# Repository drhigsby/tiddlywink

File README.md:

# tiddlywink

An angled, unibody QAZ-like 40% keyboard with 38 keys and two optional rotary encoder positions.

## Hardware

| Component | Qty | Notes |
|---|---|---|
| MX Switches | 38 | 5-pin highly recommended |
| Diodes | 38 | SOD-123 |
| Pro Micro or equivalent | 1 | ATmega32U4, USB-C recommended |
| Low Profile Binding Barrels | 5 | https://www.mcmaster.com/93121A330/ |
| RGB LEDs | 10 | Optional — WS2812B-B |
| Rotary Encoder | 1 | Optional — Alps EC11, two positions available |
| Reset Button | 1 | Optional — SMD SW_SPST_SKQG https://www.amazon.com/gp/product/B07JM32QQW/ |

## Firmware

This keyboard runs [VIAL](https://get.vial.today) firmware for live keymap editing.

Firmware source files are in the `firmware/` folder and are also submitted to [vial-qmk](https://github.com/vial-kb/vial-qmk).

To compile:
\`\`\`bash
qmk compile -kb drhigsby/tiddlywink -km vial -c
\`\`\`

## Repository Structure

\`\`\`
tiddlywink/
├── firmware/       # QMK/VIAL firmware source files
├── hardware/       # KiCad schematic and PCB files
├── gerbers/        # Gerber files for PCB fabrication
│   ├── angled/     # Original angled variant
│   └── square/     # Square variant
└── case/           # Case DXF files
\`\`\`

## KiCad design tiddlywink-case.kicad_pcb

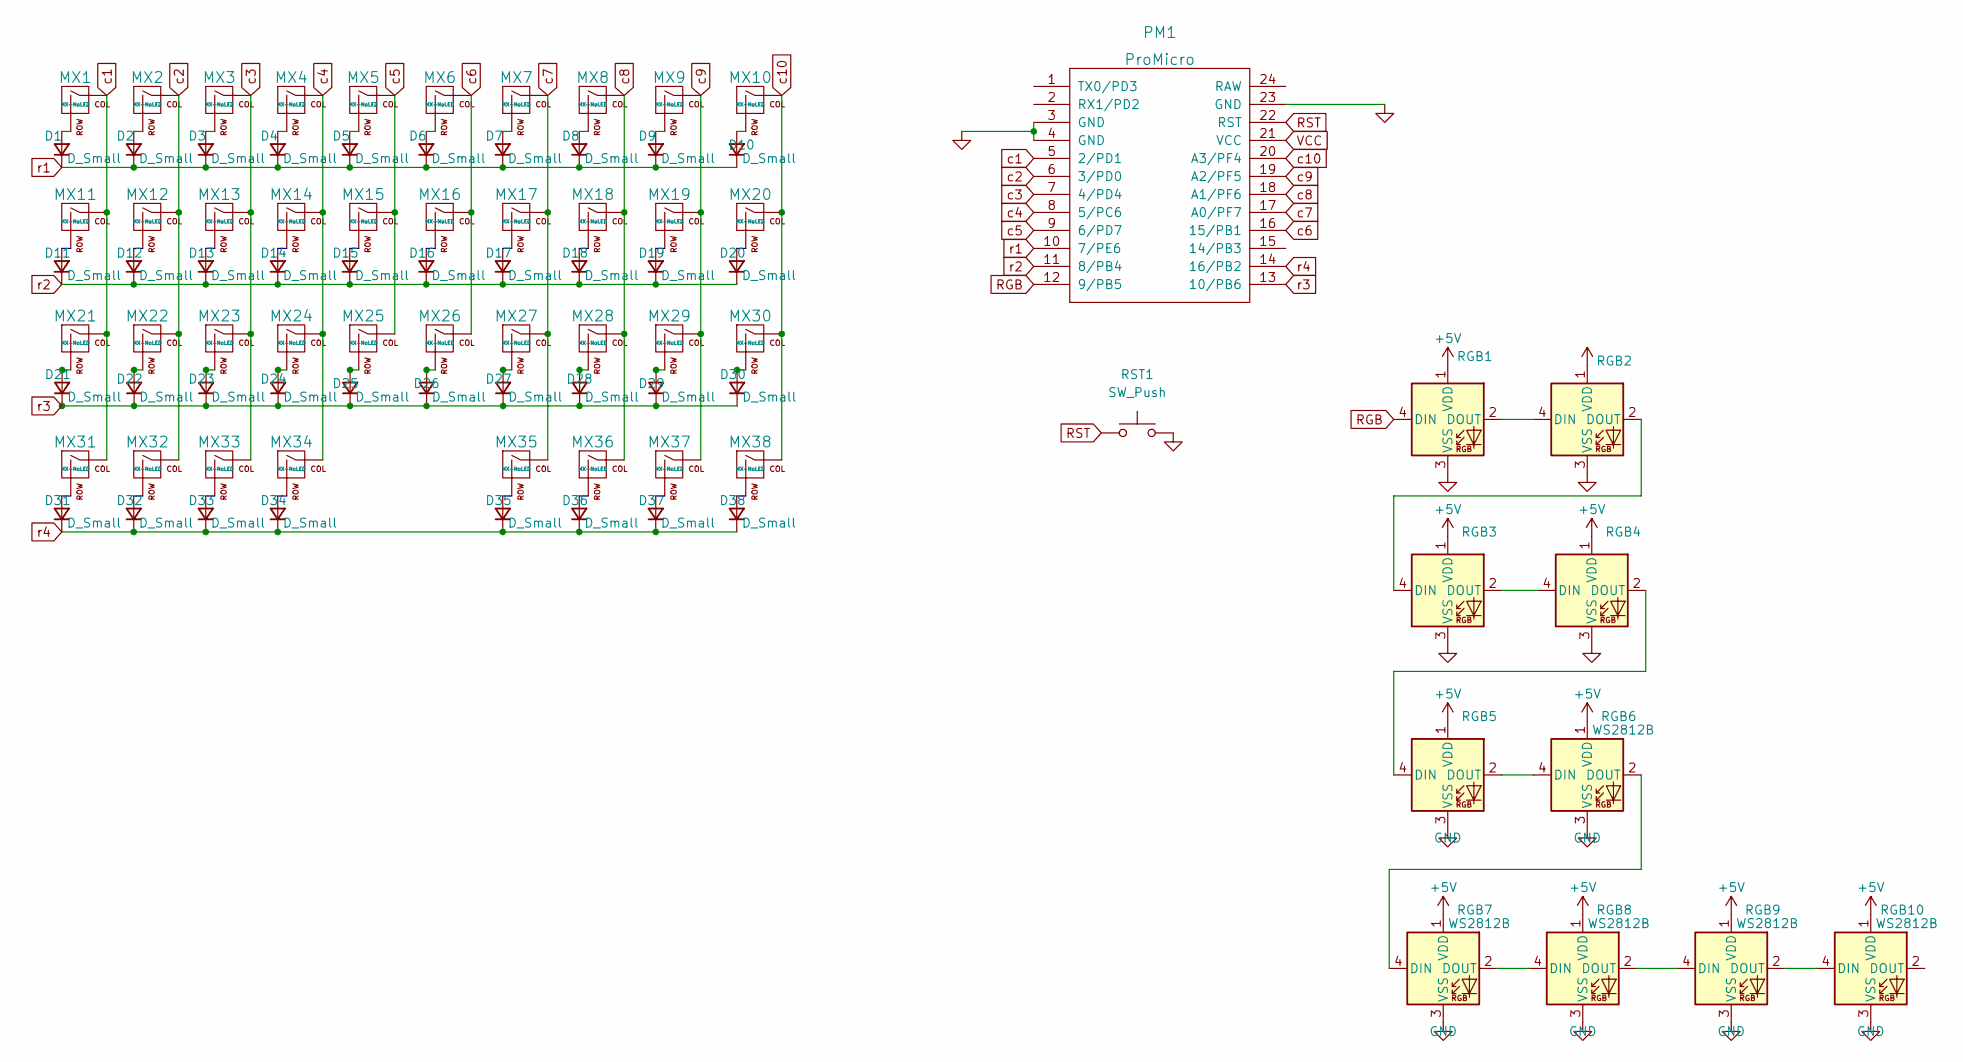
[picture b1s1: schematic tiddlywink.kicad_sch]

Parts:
D1, D2, D3, D4, D5, D6, D7, D8, D9, D10, D11, D12, D13, D14, D15, D16, D17, D18, D19, D20, D21, D22, D23, D24, D25, D26, D27, D28, D29, D30, D31, D32, D33, D34, D35, D36, D37, D38: D_Small; D_SOD123_via
MX1, MX2, MX3, MX4, MX5, MX6, MX7, MX8, MX9, MX12, MX13, MX14, MX15, MX16, MX17, MX18, MX19, MX20, MX22, MX23, MX24, MX25, MX26, MX27, MX28, MX29, MX32, MX33, MX36, MX37: MX-NoLED; MXOnly-1U-NoLED
MX10, MX11, MX31, MX38: MX-NoLED; MXOnly-1.25U-NoLED
MX21, MX34, MX35: MX-NoLED; MXOnly-1.75U-NoLED
MX30: MX-NoLED; MXOnly-1.5U-NoLED
PM1: ProMicro; ArduinoProMicro
RGB1, RGB2, RGB3, RGB4, RGB5: (no value)
RGB6, RGB7, RGB8, RGB9, RGB10: WS2812B; LED_WS2812B_PLCC4_5.0x5.0mm_P3.2mm
RST1: SW_Push; SW_SPST_TL3342

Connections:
unnamed: D1.2 (A), MX1.2 (ROW)
unnamed: D2.2 (A), MX2.2 (ROW)
unnamed: D3.2 (A), MX3.2 (ROW)
unnamed: D4.2 (A), MX4.2 (ROW)
unnamed: D5.2 (A), MX5.2 (ROW)
unnamed: D6.2 (A), MX6.2 (ROW)
unnamed: D7.2 (A), MX7.2 (ROW)
unnamed: D8.2 (A), MX8.2 (ROW)
unnamed: D9.2 (A), MX9.2 (ROW)
unnamed: D10.2 (A), MX10.2 (ROW)
unnamed: D11.2 (A), MX11.2 (ROW)
unnamed: D12.2 (A), MX12.2 (ROW)
unnamed: D13.2 (A), MX13.2 (ROW)
unnamed: D14.2 (A), MX14.2 (ROW)
unnamed: D15.2 (A), MX15.2 (ROW)
unnamed: D16.2 (A), MX16.2 (ROW)
unnamed: D17.2 (A), MX17.2 (ROW)
unnamed: D18.2 (A), MX18.2 (ROW)
unnamed: D19.2 (A), MX19.2 (ROW)
unnamed: D20.2 (A), MX20.2 (ROW)
unnamed: D21.2 (A), MX21.2 (ROW)
unnamed: D22.2 (A), MX22.2 (ROW)
unnamed: D23.2 (A), MX23.2 (ROW)
unnamed: D24.2 (A), MX24.2 (ROW)
unnamed: D25.2 (A), MX25.2 (ROW)
unnamed: D26.2 (A), MX26.2 (ROW)
unnamed: D27.2 (A), MX27.2 (ROW)
unnamed: D28.2 (A), MX28.2 (ROW)
unnamed: D29.2 (A), MX29.2 (ROW)
unnamed: D30.2 (A), MX30.2 (ROW)
unnamed: D31.2 (A), MX31.2 (ROW)
unnamed: D32.2 (A), MX32.2 (ROW)
unnamed: D33.2 (A), MX33.2 (ROW)
unnamed: D34.2 (A), MX34.2 (ROW)
unnamed: D35.2 (A), MX35.2 (ROW)
unnamed: D36.2 (A), MX36.2 (ROW)
unnamed: D37.2 (A), MX37.2 (ROW)
unnamed: D38.2 (A), MX38.2 (ROW)
unnamed: RGB1.2 (DOUT), RGB2.4 (DIN)
unnamed: RGB2.2 (DOUT), RGB3.4 (DIN)
unnamed: RGB3.2 (DOUT), RGB4.4 (DIN)
unnamed: RGB4.2 (DOUT), RGB5.4 (DIN)
unnamed: RGB5.2 (DOUT), RGB6.4 (DIN)
unnamed: RGB6.2 (DOUT), RGB7.4 (DIN)
unnamed: RGB8.2 (DOUT), RGB9.4 (DIN)
unnamed: RGB7.2 (DOUT), RGB8.4 (DIN)
unnamed: RGB9.2 (DOUT), RGB10.4 (DIN)
RGB: PM1.12 (9/PB5), RGB1.4 (DIN)
RST: PM1.22 (RST), RST1.1
VCC: PM1.21 (VCC)
c1: MX1.1 (COL), MX11.1 (COL), MX21.1 (COL), MX31.1 (COL), PM1.5 (2/PD1)
c2: MX2.1 (COL), MX12.1 (COL), MX22.1 (COL), MX32.1 (COL), PM1.6 (3/PD0)
c3: MX3.1 (COL), MX13.1 (COL), MX23.1 (COL), MX33.1 (COL), PM1.7 (4/PD4)
c4: MX4.1 (COL), MX14.1 (COL), MX24.1 (COL), MX34.1 (COL), PM1.8 (5/PC6)
c5: MX5.1 (COL), MX15.1 (COL), MX25.1 (COL), PM1.9 (6/PD7)
c6: MX6.1 (COL), MX16.1 (COL), MX26.1 (COL), PM1.16 (15/PB1)
c7: MX7.1 (COL), MX17.1 (COL), MX27.1 (COL), MX35.1 (COL), PM1.17 (A0/PF7)
c8: MX8.1 (COL), MX18.1 (COL), MX28.1 (COL), MX36.1 (COL), PM1.18 (A1/PF6)
c9: MX9.1 (COL), MX19.1 (COL), MX29.1 (COL), MX37.1 (COL), PM1.19 (A2/PF5)
c10: MX10.1 (COL), MX20.1 (COL), MX30.1 (COL), MX38.1 (COL), PM1.20 (A3/PF4)
r1: D1.1 (K), D2.1 (K), D3.1 (K), D4.1 (K), D5.1 (K), D6.1 (K), D7.1 (K), D8.1 (K), D9.1 (K), D10.1 (K), PM1.10 (7/PE6)
r2: D11.1 (K), D12.1 (K), D13.1 (K), D14.1 (K), D15.1 (K), D16.1 (K), D17.1 (K), D18.1 (K), D19.1 (K), D20.1 (K), PM1.11 (8/PB4)
r3: D21.1 (K), D22.1 (K), D23.1 (K), D24.1 (K), D25.1 (K), D26.1 (K), D27.1 (K), D28.1 (K), D29.1 (K), D30.1 (K), PM1.13 (10/PB6)
r4: D31.1 (K), D32.1 (K), D33.1 (K), D34.1 (K), D35.1 (K), D36.1 (K), D37.1 (K), D38.1 (K), PM1.14 (16/PB2)

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
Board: 2 copper layers, 87 parts (48 on the bottom side), 63 nets, no tracks yet.

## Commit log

2022-10-11 minor pcb updates
    added silk to front
    moved reset button position
    adjusted a few traces
2022-10-12 pcb update
    added additional screw hole options
2022-10-12 another update
    updated gerber and drill files for new holes
2022-10-13 big update
    added rgb support
    updated case files
2022-10-27 Rotary Encoder Support
    added rotary encoder support on B and second B
    moved some diodes
    updated traces to match
    updated gerber files
2022-10-31 updated PCB
    changed pcb shape
    removed older pcb shape
2022-11-02 updated case files
    added case file dxfs to kicad files on various layers:
    -user.eco1
    -user.1
    -user.2
    -user.3
2022-11-03 updated case files
    updated dxf files to be more precise
2023-09-30 fix rgb
    uses vcc symbol in schematic
    connects vcc from pro micro to rgbs
    connects disconnected gnd fill with vias
2026-05-16 reorganize repo: clean up structure, add firmware, update README
